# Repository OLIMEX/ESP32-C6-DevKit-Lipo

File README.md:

# MOD-ESP32-C6-DevKit-Lipo
ESP32-C6 WiFi6, Bluetooth 5 LE, Zigbee, Thread Matter breadboard friendly development board with Lipo charger and UEXT module

https://www.olimex.com/Products/IoT/ESP32-C6/ESP32-C6-DevKit-Lipo/

## Licensee
* Hardware is released under CERN Open Hardware Licence Version 2 - Strongly Reciprocal
* Software is released under MIT Licensee
* Documentation is released under CC BY-SA 4.0

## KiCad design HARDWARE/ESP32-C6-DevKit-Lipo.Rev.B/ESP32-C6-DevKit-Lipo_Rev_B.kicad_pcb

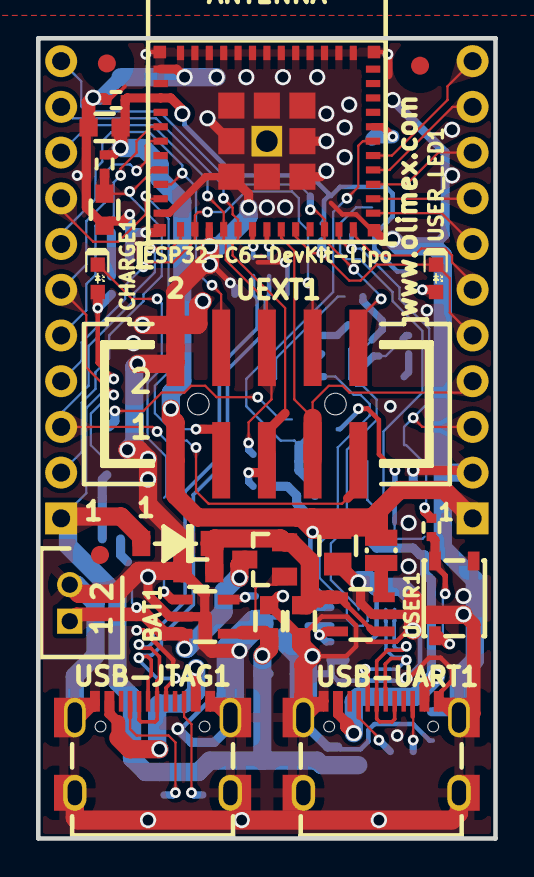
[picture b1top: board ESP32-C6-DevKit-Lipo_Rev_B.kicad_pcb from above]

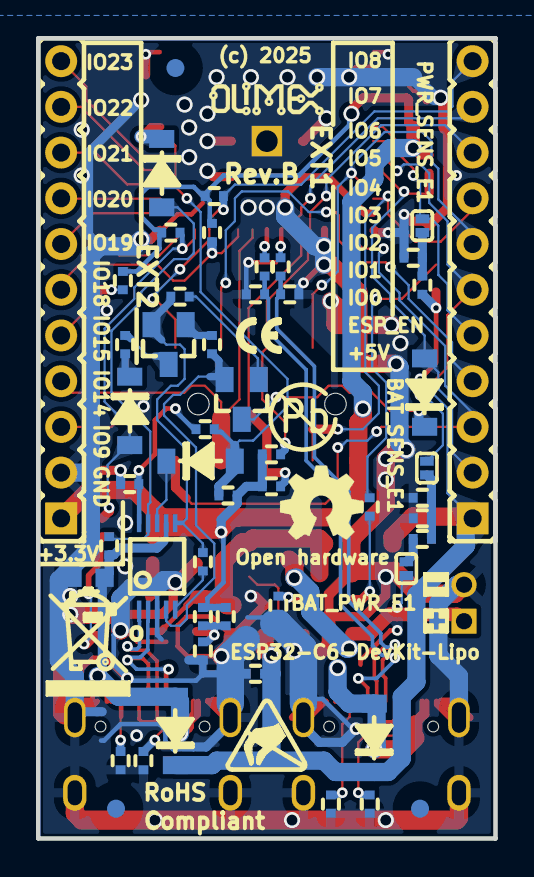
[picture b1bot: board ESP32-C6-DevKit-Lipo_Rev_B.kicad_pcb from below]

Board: 2 copper layers, 25.4 x 44.5 mm, 84 parts (59 on the bottom side), 59 nets.

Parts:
+ Sign: + Sign
- Sign: - Sign
BAT1: DW02S; LIPO_BAT_VERTICAL_DW02S
BAT_PWR_E1: Opened; SJ_1_SMALLER
BAT_SENS_E1: Opened; SJ_1_SMALLER
C1, C7, C11, C14: 22uF/6.3V/20%/X5R/C0603; C_0603_5MIL_DWS
C2, C4, C12: 100nF/10V/20%/X5R/C0402; C_0402_5MIL_DWS
C3: 1uF/10V/10%/X5R/C0603; C_0603_5MIL_DWS
C5, C6: 150pF/50V/2%/NP0/C0402; C_0402_5MIL_DWS
C8: 47uF/6.3V/20%/X5R/C0805; C_0805_5MIL_DWS
C9: NA(120pF/50V/5%/C0G/C0402); C_0402_5MIL_DWS
C10: NA(22uF/6.3V/20%/X5R/C0603); C_0603_5MIL_DWS
CHARGE1: LED/Yellow/0603; LED_0603_KA
D1, D2, D3, D4, D5, D6, D7: 1N5819S4(SOD-123); SOD-123_1C-2A_KA
EXT1, EXT2: HN1x11
FET1: IRLML6402TRPbF; SOT23
FID1, FID2, FID4, FID5: Fiducial; Fiducial1x3
FID3, FID6: Fiducial; Fiducial1x3_Paste
L1: 2.2uH/2.8A/DCR=120mR/20%/2.00x1.60x1.00mm/L2016(P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; L_2016_MM
Logo_OLIMEX_80: Logo_OLIMEX_80
PWR_SENS_E1: Opened; SJ_1_SMALLER
Q1, Q2: BC817-40(SOT23); SOT23
R1: 220k/R0402; R_0402_5MIL_DWS
R2, R4, R9, R10, R18, R19: 10k/R0402; R_0402_5MIL_DWS
R3, R5, R6: 470k/R0402; R_0402_5MIL_DWS
R7, R8, R12, R21: 2.2k/R0402; R_0402_5MIL_DWS
R11, R20: NA(10k/R0402); R_0402_5MIL_DWS
R13, R14: 22R/R0402; R_0402_5MIL_DWS
R15: 180k/1%/R0402; R_0402_5MIL_DWS
R16: 10k/1%/R0402; R_0402_5MIL_DWS
R17: 40.2k/1%/R0402; R_0402_5MIL_DWS
R22, R28: 1k/R0402; R_0402_5MIL_DWS
R23: 4.7k/R0402; R_0402_5MIL_DWS
R24, R25, R26, R27: 5.1k/1%/R0402; R_0402_5MIL_DWS
R29: 100R/R0402; R_0402_5MIL_DWS
R30: 220R/R0402; R_0402_5MIL_DWS
Sign_Antistatic_Small: Sign_Antistatic; Sign_Antistatic_4.5mmX2.8mm
Sign_CE_Small: CE_Sign_Small
Sign_OSHW_7.3x6.0mm: Sign_OSHW_7.3x6.0mm; Sign_OSHW_7.3x6.0mmn
Sign_PB-Free: Sign_PB-Free
Sign_RecycleBin_1: Sign_RecycleBin_1
U1: ESP32-C6-MINI-1-N4
U2: SY8089AAAC(SOT23-5); SOT-23-5
U3: TP4054-42-SOT25-R; SOT-23-5
U4: CH340X(MSOP-10); MSOP-10_Pitch-0.5mm_3.00x3.00x1.00mm
UEXT1: P-B-V-10-LF; GBH-254-SMT-10
USB-JTAG1: USB-C-16P-F(A40-00119-A52-12); USB2.0_TYPE-C(A40-00119-A52-12)_Paste
USB-UART1: USB-C-16P-F(A40-00119-A52-12); USB2.0_TYPE-C(A40-00119-A52-12)_Paste
USER1: YTS-A016-X
USER_LED1: LED/GREEN/0603; LED_0603_KA

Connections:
+3.3V: C1.1, C2.1, C8.1, C9.2, EXT2.1, L1.2, R2.1, R7.1, R8.1, R9.1, R10.1, R11.2, R15.2, R20.2, R21.1, U1.3 (3V3), UEXT1.1
+5V: C14.1, CHARGE1.2 (A), D1.2 (A), D2.1 (K), D3.1 (K), EXT1.1, FET1.1, R1.1, R4.1, U3.4 (VCC)
/D+: U4.1 (UD+), USB-UART1.A6 (DP1), USB-UART1.B6 (DP2)
/D-: U4.2 (UD-), USB-UART1.A7 (DN1), USB-UART1.B7 (DN2)
/ESP_EN: C3.1, D6.2 (A), EXT1.2, R2.2, U1.8 (EN)
/GPIO0/CLK: EXT1.3, U1.12 (IO0/GPIO0/XTAL_32K_P/LP_GPIO0/LP_UART_D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), UEXT1.9
/GPIO1/MOSI: EXT1.4, U1.13 (IO1/GPIO1/XTAL_32K_N/LP_GPIO1/LP_UART_D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), UEXT1.8
/GPIO2/EXT_POWER: EXT1.5, PWR_SENS_E1.2, U1.5 (IO2/GPIO2/LP_GPIO2/LP_UART_RTSN/ADC1_CH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)
/GPIO3/BAT_MEASURE: BAT_SENS_E1.2, EXT1.6, U1.6 (IO3/GPIO3/LP_GPIO3/LP_UART_CTSN/ADC1_CH3)
/GPIO4/LP_UART_RXD: EXT1.7, U1.9 (IO4/GPIO4/LP_GPIO4/LP_UART_RXD/MTMS/ADC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), UEXT1.4
/GPIO5/LP_UART_TXD: EXT1.8, U1.10 (IO5/GPIO5/LP_GPIO5/LP_UART_TXD/MTDI/ADC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), UEXT1.3
/GPIO6/LP_I2C_SDA: EXT1.9, R7.2, U1.15 (IO6/GPIO6/MTCK/LP_GPIO6/LP_I2C_SDA/ADC1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), UEXT1.6
/GPIO7/LP_I2C_SCL: EXT1.10, R8.2, U1.16 (IO7/GPIO7/MTDO/LP_GPIO7/LP_I2C_SCL/FSPID), UEXT1.5
/GPIO8/CS: EXT1.11, R9.2, U1.22 (IO8/GPIO8), UEXT1.10
/GPIO9/USER_BUT: D7.2 (A), EXT2.3, R10.2, R29.1, U1.23 (IO9/GPIO9)
/GPIO14/MISO: EXT2.4, U1.19 (IO14/GPIO14), UEXT1.7
/GPIO15/USER_LED1: EXT2.5, R11.1, U1.20 (IO15/GPIO15), USER_LED1.1 (K)
/GPIO18: EXT2.6, U1.24 (IO18/GPIO18/SDIO_CMD/FSPICS2)
/GPIO19: EXT2.7, U1.25 (IO19/GPIO19/SDIO_CLK/FSPICS3)
/GPIO20: EXT2.8, U1.26 (IO20/GPIO20/SDIO_DATA0/FSPICS4)
/GPIO21: EXT2.9, U1.27 (IO21/GPIO21/SDIO_DATA1/FSPICS5)
/GPIO22: EXT2.10, U1.28 (IO22/GPIO22/SDIO_DATA2)
/GPIO23: EXT2.11, U1.29 (IO23/GPIO23/SDIO_DATA3)
/U0RXD: D4.2 (A), R19.2, R20.1, U1.30 (RXD0/U0RXD/GPIO17/FSPICS1)
/U0TXD: D5.1 (K), U1.31 (TXD0/U0TXD/GPIO16/FSPICS0)
/USB_D+: C5.1, R14.2, USB-JTAG1.A6 (DP1), USB-JTAG1.B6 (DP2)
/USB_D-: C6.1, R13.1, USB-JTAG1.A7 (DN1), USB-JTAG1.B7 (DN2)
GND: BAT1.2, C1.2, C2.2, C3.2, C4.1, C5.2, C6.2, C7.2, C8.2, C10.2, C11.2, C12.2, C14.2, EXT2.2, R4.2, R5.2, R6.2, R16.1, R17.2, R24.1, R25.1, R26.1, R27.1, U1.1 (GND), U1.2 (GND), U1.11 (GND), U1.14 (GND), U1.36 (GND), U1.37 (GND), U1.38 (GND), U1.39 (GND), U1.40 (GND), U1.41 (GND), U1.42 (GND), U1.43 (GND), U1.44 (GND), U1.45 (GND), U1.46 (GND), U1.47 (GND), U1.48 (GND), U1.49 (GND), U1.50 (GND), U1.51 (GND), U1.52 (GND), U1.53 (GND), U2.2 (GND), U3.2 (GND), U4.3 (GND), UEXT1.2, USB-JTAG1.0 (SHELL), USB-JTAG1.A1 (GND), USB-JTAG1.A12 (GND), USB-JTAG1.B1 (GND), USB-JTAG1.B12 (GND), USB-UART1.0 (SHELL), USB-UART1.A1 (GND), USB-UART1.A12 (GND), USB-UART1.B1 (GND), USB-UART1.B12 (GND), USER1.1
unnamed: BAT_PWR_E1.1, R3.1
unnamed: BAT_SENS_E1.1, C4.2, R3.2, R6.1
unnamed: CHARGE1.1 (K), R12.2
unnamed: C7.1, C10.1, D1.1 (K), FET1.2, U2.1 (EN), U2.4 (IN)
unnamed: C11.1, D2.2 (A), R18.1, U4.7 (VCC), USB-UART1.A4 (VBUS), USB-UART1.A9 (VBUS), USB-UART1.B4 (VBUS), USB-UART1.B9 (VBUS)
unnamed: D3.2 (A), USB-JTAG1.A4 (VBUS), USB-JTAG1.A9 (VBUS), USB-JTAG1.B4 (VBUS), USB-JTAG1.B9 (VBUS)
unnamed: D4.1 (K), U4.8 (TXD)
unnamed: D5.2 (A), R18.2, U4.9 (RXD)
unnamed: D6.1 (K), Q1.3 (C)
unnamed: D7.1 (K), R30.2
unnamed: PWR_SENS_E1.1, R1.2, R5.1
unnamed: Q1.1 (B), R22.2
unnamed: Q1.2 (E), R28.1, U4.4 (RTS#)
unnamed: Q2.1 (B), R28.2
unnamed: Q2.3 (C), R30.1
unnamed: Q2.2 (E), R22.1, R23.1, U4.6 (TNOW/DTR#)
unnamed: R29.2, USER1.2
unnamed: R13.2, U1.17 (IO12/GPIO12/USB_D-)
unnamed: R14.1, U1.18 (IO13/GPIO13/USB_D+)
unnamed: C9.1, R15.1, R17.1, U2.5 (FB)
unnamed: L1.1, U2.3 (LX)
unnamed: R12.1, U3.1 (CHRGb)
unnamed: R16.2, U3.5 (PROG)
unnamed: R23.2, U4.5 (CTS#)
unnamed: C12.1, R19.1, U4.10 (V3)
unnamed: R27.2, USB-JTAG1.A5 (CC1)
unnamed: R26.2, USB-JTAG1.B5 (CC2)
unnamed: R25.2, USB-UART1.A5 (CC1)
unnamed: R24.2, USB-UART1.B5 (CC2)
unnamed: R21.2, USER_LED1.2 (A)
VBAT: BAT1.1, BAT_PWR_E1.2, FET1.3, U3.3 (VBAT)

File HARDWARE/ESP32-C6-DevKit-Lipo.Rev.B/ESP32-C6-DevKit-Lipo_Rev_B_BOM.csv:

"Id";"Designator";"Footprint";"Quantity";"Designation";"Supplier and ref";
1;"CHARGE1";"LED_0603_KA";1;"LED/Yellow/0603";;;
2;"C14,C1,C7,C11";"C_0603_5MIL_DWS";4;"22uF/6.3V/20%/X5R/C0603";;;
3;"FID3,FID6";"Fiducial1x3_Paste";2;"Fiducial";;;
4;"C2,C4,C12";"C_0402_5MIL_DWS";3;"100nF/10V/20%/X5R/C0402";;;
5;"C3";"C_0603_5MIL_DWS";1;"1uF/10V/10%/X5R/C0603";;;
6;"USER_LED1";"LED_0603_KA";1;"LED/GREEN/0603";;;
7;"U2";"SOT-23-5";1;"SY8089AAAC(SOT23-5)";;;
8;"USB-JTAG1,USB-UART1";"USB2.0_TYPE-C(A40-00119-A52-12)_Paste";2;"USB-C-16P-F(A40-00119-A52-12)";;;
9;"R29";"R_0402_5MIL_DWS";1;"100R/R0402";;;
10;"UEXT1";"GBH-254-SMT-10";1;"P-B-V-10-LF";;;
11;"U1";"ESP32-C6-MINI-1-N4";1;"ESP32-C6-MINI-1-N4";;;
12;"R2,R19,R18,R4,R9,R10";"R_0402_5MIL_DWS";6;"10k/R0402";;;
13;"U3";"SOT-23-5";1;"TP4054-42-SOT25-R";;;
14;"FID1,FID2,FID4,FID5";"Fiducial1x3";4;"Fiducial";;;
15;"C8";"C_0805_5MIL_DWS";1;"47uF/6.3V/20%/X5R/C0805";;;
16;"D1,D5,D2,D7,D3,D4,D6";"SOD-123_1C-2A_KA";7;"1N5819S4(SOD-123)";;;
17;"FET1";"SOT23";1;"IRLML6402TRPbF";;;
18;"BAT1";"LIPO_BAT_VERTICAL_DW02S";1;"DW02S";;;
19;"C10";"C_0603_5MIL_DWS";1;"NA(22uF/6.3V/20%/X5R/C0603)";;;
20;"L1";"L_2016_MM";1;"2.2uH/2.8A/DCR=120mR/20%/2.00x1.60x1.00mm/L2016(PIM201610-2R2MTS00)";;;
21;"USER1";"YTS-A016-X";1;"YTS-A016-X";;;
22;"C5,C6";"C_0402_5MIL_DWS";2;"150pF/50V/2%/NP0/C0402";;;
23;"Q1,Q2";"SOT23";2;"BC817-40(SOT23)";;;
24;"R17";"R_0402_5MIL_DWS";1;"40.2k/1%/R0402";;;
25;"R27,R26,R25,R24";"R_0402_5MIL_DWS";4;"5.1k/1%/R0402";;;
26;"R22,R28";"R_0402_5MIL_DWS";2;"1k/R0402";;;
27;"PWR_SENS_E1,BAT_PWR_E1,BAT_SENS_E1";"SJ_1_SMALLER";3;"Opened";;;
28;"R3,R5,R6";"R_0402_5MIL_DWS";3;"470k/R0402";;;
29;"R23";"R_0402_5MIL_DWS";1;"4.7k/R0402";;;
30;"C9";"C_0402_5MIL_DWS";1;"NA(120pF/50V/5%/C0G/C0402)";;;
31;"R16";"R_0402_5MIL_DWS";1;"10k/1%/R0402";;;
32;"R15";"R_0402_5MIL_DWS";1;"180k/1%/R0402";;;
33;"EXT1,EXT2";"HN1x11";2;"HN1x11";;;
34;"U4";"MSOP-10_Pitch-0.5mm_3.00x3.00x1.00mm";1;"CH340X(MSOP-10)";;;
35;"R20,R11";"R_0402_5MIL_DWS";2;"NA(10k/R0402)";;;
36;"R7,R12,R21,R8";"R_0402_5MIL_DWS";4;"2.2k/R0402";;;
37;"R30";"R_0402_5MIL_DWS";1;"220R/R0402";;;
38;"R13,R14";"R_0402_5MIL_DWS";2;"22R/R0402";;;
39;"R1";"R_0402_5MIL_DWS";1;"220k/R0402";;;

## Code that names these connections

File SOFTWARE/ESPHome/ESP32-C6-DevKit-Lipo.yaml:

esphome:
  name: esp32-c6-devkit-lipo
  friendly_name: ESP32-C6-DevKit-Lipo

esp32:
  board: esp32-c6-devkitc-1
  variant: esp32c6
  framework:
    type: arduino

# ============================================================
# LOGGING / CONTROL
# ============================================================
logger:
api:
ota:
captive_portal:

wifi:
  ssid: "YOUR_SSID"
  password: "YOUR_PASSWORD"
  ap:
    ssid: "ESP32-C6-DevKit-Lipo Fallback"
    password: "12345678"

# ============================================================
# 🔴 USER LED — GPIO15
# ============================================================
output:
  - platform: gpio
    pin: GPIO15
    id: user_led_output

light:
  - platform: binary
    name: "ESP32-C6-DevKit-Lipo User LED"
    output: user_led_output

# ============================================================
# 🔘 USER BUTTON — GPIO9
# ============================================================
binary_sensor:
  - platform: gpio
    name: "ESP32-C6-DevKit-Lipo User Button"
    pin:
      number: GPIO9
      mode:
        input: true
        pullup: true
      inverted: true
    on_press:
      - light.toggle: user_led_output

# ============================================================
# 🔌 UEXT I2C — GPIO7 SCL / GPIO6 SDA
# ============================================================
i2c:
  sda: GPIO6
  scl: GPIO7
  scan: true

# ============================================================
# 🔌 UEXT SPI BUS
# ============================================================
spi:
  clk_pin: GPIO0
  mosi_pin: GPIO1
  miso_pin: GPIO14

# Chip Select pin available for devices:
# GPIO8

# ============================================================
# 🔌 UEXT UART — GPIO5 TX / GPIO4 RX
# ============================================================
uart:
  - id: uext_uart
    tx_pin: GPIO5
    rx_pin: GPIO4
    baud_rate: 115200

# ============================================================
# 🔋 BATTERY VOLTAGE — GPIO3 (jumpers must be closed)
# Divider: 470k / 470k → ×2 scaling
# ============================================================
sensor:
  - platform: adc
    pin: GPIO3
    name: "ESP32-C6-DevKit-Lipo Battery Voltage"
    attenuation: 11db
    update_interval: 30s
    filters:
      - multiply: 2.0
    unit_of_measurement: "V"
    accuracy_decimals: 2
    device_class: voltage
    state_class: measurement

# ============================================================
# 🔌 EXTERNAL POWER SENSE — GPIO2 (jumpers required)
# ============================================================
binary_sensor:
  - platform: gpio
    name: "ESP32-C6-DevKit-Lipo External Power"
    pin:
      number: GPIO2
      mode: input

# ============================================================
# HARDWARE NOTES — ESP32-C6-DevKit-Lipo
# ============================================================
# CH340 USB-UART uses GPIO16 (TX) and GPIO17 (RX)
# Avoid using these pins if programming over that port.
#
# GPIO0, GPIO8 are boot-related + SPI — keep stable at boot.
# No PSRAM on ESP32-C6-MINI-1-N4.
# ADC range is 0–3.3V only.

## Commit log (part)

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2025-12-05 initial upload
2025-12-05 add user manual
2026-02-11 Update
    Added PlatformIO and ESPHome configs

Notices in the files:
HARDWARE/ESP32-C6-DevKit-Lipo.Rev.B/ESP32-C6-DevKit-Lipo_Rev_B.kicad_pcb:
(c) 2025
